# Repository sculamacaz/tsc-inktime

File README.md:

# InkTime

Author: Luca Mazilescu

## Block Diagram

## Hardware Functionality

### Microcontroller

The system is built around a Nordic **nRF52840** SoC (Arm Cortex-M4F @ 64 MHz, 1 MB flash, 256 kB RAM). It was chosen because it integrates a 2.4 GHz radio supporting Bluetooth Low Energy alongside a USB 2.0 full-speed controller, which covers both the wireless sync path and the USB-C data path without any external transceiver. The MCU runs from a 32 MHz high-frequency crystal (XC1/XC2) for the radio and CPU, and a 32.768 kHz low-frequency crystal (XL1/XL2) for the RTC and low-power sleep timing — accurate timekeeping is the whole point of a watch, so the LFXO is not optional.

An on-board 2.4 GHz chip antenna (2450AT18B100E) is placed at the edge of the PCB with a keep-out area underneath, fed from the `ANT` pin through a matching network.

### Display — E-Paper (SPI)

A reflective e-paper display is driven over **SPI** using SCK (P0.02), MOSI (P0.03) and a dedicated chip-select (P0.05). Three auxiliary GPIOs handle the panel-specific control lines: `EPD_DC` (P0.15) switches between command and data bytes, `EPD_RST` (P0.16) resets the display controller, and `EPD_BUSY` (P0.17) is an input the MCU polls while the panel completes a refresh. The display connects through a 24-pin FPC.

Because e-paper draws current only during a refresh (and essentially zero while displaying a static image), the entire display rail is gated by a PFET whose gate is driven from P1.01. Firmware can therefore cut power to the panel completely between updates, which is the dominant reason this watch can be expected to last days on a charge rather than hours.

### IMU — BMA421 (I²C)

A Bosch **BMA421** 3-axis accelerometer sits on the shared I²C bus. It provides raw acceleration data plus on-chip step counting functionality. Two interrupt lines, `IMU_INT1` (P0.08) and `IMU_INT2` (P1.08), let the sensor wake the MCU from deep sleep when a gesture or step event occurs, so the CPU does not have to poll the bus continuously.

### Haptics — DRV2605 (I²C)

A TI **DRV2605L** haptic driver actuates a coin LRA/ERM motor for notifications and UI feedback. It is configured over I²C and can play back effects from its internal ROM library, so the MCU only issues short "play effect N" commands rather than streaming waveforms. An enable line (`HAPTIC_EN`, P0.12) lets the MCU fully power the driver down when idle.

### Power management — BQ25180 + MAX17048 + RT6160

USB-C provides 5 V in through a USBLC6-2SC6Y ESD protector, with the two required 5.1 kΩ CC pull-downs advertising the device as a sink. A **BQ25180** single-cell Li-ion charger manages the LiPo battery: it handles CC/CV charging from USB, switches between USB and battery as the system source, and reports faults over I²C and on the `PMIC_INT` line (P0.11).

The system rail is generated by an **RT6160** buck-boost regulator producing a stable `3V3` across the full battery voltage range (~3.0–4.2 V), which is important because a plain buck would drop out near end-of-discharge and a plain boost would waste efficiency when the cell is full.

State-of-charge is tracked by a **MAX17048** fuel gauge directly on the battery node. It uses Maxim's ModelGauge algorithm, so no external current-sense resistor is needed — the MCU just reads the remaining percentage and cell voltage over I²C, and an `ALERT` line (P1.10) fires on programmable under/over-voltage thresholds.

### Inputs — Buttons

Three user buttons are connected to P0.13, P0.14 and P1.02 as active-low inputs with RC debounce. They use the MCU's internal pull-ups and can trigger GPIOTE interrupts to wake the device from System OFF.

### Shared I²C bus

All four I²C peripherals (BMA421, MAX17048, DRV2605L, BQ25180) share a single bus on SDA (P0.06) and SCL (P0.07), with 3.3 kΩ pull-ups to `3V3`. The devices have distinct 7-bit addresses, so one TWI instance on the nRF52840 is sufficient. Running I²C at 400 kHz (Fast-mode) is more than enough headroom for the low-bandwidth status reads these sensors require.

### Debug

An SWD interface (`SWDCLK`, `SWDIO`, optional `SWO` on P1.00) is exposed through a Tag-Connect TC2030 footprint, which avoids placing a bulky 2×5 header on a wearable-sized PCB.

### Expected capabilities

With the hardware described above, firmware would be able to: keep accurate time from the LFXO-backed RTC, render watch faces and menus on the e-paper display, detect steps and wrist-raise via the BMA421, deliver haptic notifications, communicate with a phone over BLE, enumerate as a USB device for charging and data, and report battery percentage and charger state in real time.

## Pinout Table

| Pin | Signal | Direction | Peripheral | Description |
|-----|--------|-----------|------------|-------------|
| P0.02 | SPI_SCK | Output | E-Paper Display | SPI clock |
| P0.03 | SPI_MOSI | Output | E-Paper Display | SPI data out |
| P0.05 | EPD_CS | Output | E-Paper Display | Chip select |
| P0.06 | SDA | Bidir | Fuel Gauge, Charger, IMU, Haptics | Shared I2C data |
| P0.07 | SCL | Output | Fuel Gauge, Charger, IMU, Haptics | Shared I2C clock |
| P0.08 | IMU_INT1 | Input | IMU (BMA421) | Interrupt line 1 |
| P0.11 | PMIC_INT | Input | Charger (BQ25180) | Fault/status interrupt |
| P0.12 | HAPTIC_EN | Output | Haptics (DRV2605) | Driver enable |
| P0.13 | — | Input | Button 1 | User button |
| P0.14 | — | Input | Button 2 | User button |
| P0.15 | EPD_DC | Output | E-Paper Display | Data/command select |
| P0.16 | EPD_RST | Output | E-Paper Display | Display reset |
| P0.17 | EPD_BUSY | Input | E-Paper Display | Busy status |
| P0.18 | RESET | Input | — | System reset |
| P1.00 | SWO | Output | Debug (pad) | SWD trace output |
| P1.01 | — | Output | EPD power gate | EPD power control |
| P1.02 | — | Input | Button 3 | User button |
| P1.08 | IMU_INT2 | Input | IMU (BMA421) | Interrupt line 2 |
| P1.10 | ALERT | Input | Fuel Gauge (MAX17048) | UV/OV alert |
| D+ | D+ | Bidir | USB-C connector | USB data+ |
| D− | D- | Bidir | USB-C connector | USB data− |
| XL1/XL2 | — | — | 32.768 kHz crystal | Low-frequency clock |
| XC1/XC2 | — | — | 32 MHz crystal | High-frequency clock |
| SWDCLK | SWDCLK | Input | Debug (pad) | SWD clock |
| SWDIO | SWDIO | Bidir | Debug (pad) | SWD data |
| ANT | RF | Output | 2.4 GHz antenna | Wireless antenna feed |

## Bill of Materials

The full, JLCPCB validated table can be found in `Assets/JLCPCB_BOM.xlsx`. That version contains detailed information about each part, such as the associated schematic designators, descriptions, and more.

| Part Name |Qty|Link (Order + Datasheet)|
| :-- | :--: | :--: |
|BMA421|1|[Link](https://jlcpcb.com/partdetail/BoschSensortec-BMA421/C5242966)|
|0201X104K100NT|5|[Link](https://jlcpcb.com/partdetail/270391-0201X104K100NT/C284966)|
|CGA0402X5R475M250GT|1|[Link](https://jlcpcb.com/partdetail/HRE-CGA0402X5R475M250GT/C6119795)|
|KH-TYPE-C-16P|1|[Link](https://jlcpcb.com/partdetail/Shenzhen_KinghelmElec-KH_TYPE_C16P/C709357)|
|RT6160AWSC|1|[Link](https://jlcpcb.com/partdetail/RichtekTech-RT6160AWSC/C7065276)|
|SDFL1608S100KTF|1|[Link](https://jlcpcb.com/partdetail/Sunlord-SDFL1608S100KTF/C1035)|
|0201WMF220KTEE|1|[Link](https://jlcpcb.com/partdetail/479910-0201WMF220KTEE/C473517)|
|EVPAKE31A|3|[Link](https://jlcpcb.com/partdetail/PANASONIC-EVPAKE31A/C569760)|
|GRM033R61A104KE15D|5|[Link](https://jlcpcb.com/partdetail/MurataElectronics-GRM033R61A104KE15D/C76934)|
|5034802400|1|[Link](https://jlcpcb.com/partdetail/MOLEX-5034802400/C122434)|
|CM8V-T1A-32.768KHZ-9PF-20PPM-TB-QA|1|[Link](https://jlcpcb.com/partdetail/C5366546)|
|BQ25180YBGR|1|[Link](https://jlcpcb.com/partdetail/TexasInstruments-BQ25180YBGR/C3682423)|
|DRV2605YZFR|1|[Link](https://jlcpcb.com/partdetail/TexasInstruments-DRV2605YZFR/C81079)|
|2450AT18B100E|1|[Link](https://jlcpcb.com/partdetail/JohansonDielectrics-2450AT18B100E/C2917717)|
|SI1308EDL-T1-GE3|1|[Link](https://jlcpcb.com/partdetail/VishayIntertech-SI1308EDL_T1GE3/C469327)|
|GRM155R60J226ME11D|2|[Link](https://jlcpcb.com/partdetail/408393-GRM155R60J226ME11D/C415703)|
|GRM155R61H105KE05D|9|[Link](https://jlcpcb.com/partdetail/1609005-GRM155R61H105KE05D/C1518208)|
|SDCL1005C15NJTDF|1|[Link](https://jlcpcb.com/partdetail/Sunlord-SDCL1005C15NJTDF/C27143)|
|0201WMJ0000TEE|3|[Link](https://jlcpcb.com/partdetail/259867-0201WMJ0000TEE/C270337)|
|CC0201KRX5R7BB473|1|[Link](https://jlcpcb.com/partdetail/YAGEO-CC0201KRX5R7BB473/C505465)|
|CL05A475MP5NRNC|5|[Link](https://jlcpcb.com/partdetail/24469-CL05A475MP5NRNC/C23733)|
|CL05A105KA5NQNC|6|[Link](https://jlcpcb.com/partdetail/53938-CL05A105KA5NQNC/C52923)|
|SDCL1005C3N9STDF|1|[Link](https://jlcpcb.com/partdetail/Sunlord-SDCL1005C3N9STDF/C14033)|
|CR0201FH5101G|2|[Link](https://jlcpcb.com/partdetail/LIZElec-CR0201FH5101G/C100142)|
|GRM0335C1H1R0BA01D|2|[Link](https://jlcpcb.com/partdetail/MurataElectronics-GRM0335C1H1R0BA01D/C85893)|
|CL05A106MQ5NUNC|3|[Link](https://jlcpcb.com/partdetail/16204-CL05A106MQ5NUNC/C15525)|
|0201CG120J500NT|4|[Link](https://jlcpcb.com/partdetail/51400-0201CG120J500NT/C50391)|
|BQ25180YBGR|1|[Link](https://jlcpcb.com/partdetail/TexasInstruments-BQ25180YBGR/C3682423)|
|MAX17048G+T10|1|[Link](https://jlcpcb.com/partdetail/2777647-MAX17048GT10/C2682616)|
|NX2016SA-32MHZ-STD-CZS-5|1|[Link](https://jlcpcb.com/partdetail/NDK-NX2016SA_32MHZ_STD_CZS5/C843260)|
|0201WMJ0332TEE|2|[Link](https://jlcpcb.com/partdetail/259848-0201WMJ0332TEE/C270318)|
|MBR0530|3|[Link](https://jlcpcb.com/partdetail/78464-MBR0530/C77336)|
|FTC252012SR47MBCA|1|[Link](https://jlcpcb.com/partdetail/6763488-FTC252012SR47MBCA/C5832368)|
|DMG2305UX-7|1|[Link](https://jlcpcb.com/partdetail/DiodesIncorporated-DMG2305UX7/C150470)|
|USBLC6-2SC6Y|1|[Link](https://jlcpcb.com/partdetail/TECHPUBLIC-USBLC62SC6Y/C5310974)|
|UCR006YVPFLR470|1|[Link](https://jlcpcb.com/partdetail/ROHMSemicon-UCR006YVPFLR470/C2089071)|
|CPF0201D10KC1|6|[Link](https://jlcpcb.com/partdetail/TEConnectivity-CPF0201D10KC1/C4187156)|
|744043680|1|[Link](https://jlcpcb.com/partdetail/WurthElektronik-744043680/C2045671)|
|GRM0335C1H101JA01D|1|[Link](https://jlcpcb.com/partdetail/MurataElectronics-GRM0335C1H101JA01D/C76922)|
|NRF52840-QIAA-R7|1|[Link](https://jlcpcb.com/partdetail/NordicSemicon-NRF52840_QIAAR7/C1851953)|

## Renders

## Design Details

### Schematic and Components

The reference schematic was double-checked with information from each component's datasheet.
Mismatches were flagged and investigated, usually stemming from older versions of the reference circuits being used by the reference schematic.

### PCB Layout and Routing

Manufacturing parameters were kept within the ranges recommended by JLCPCB's standard rigid PCB assembly service.

A top ground pour was stitched to the ground plane, and more granular manual stitching was performed around the antenna feed line.

Teardrops were generated at most trace joints, and angles were carefully considered during routing.
Since Fusion exhibits buggy behavior when generating teardrops for off-grid rotations,
the shapes were manually smoothed for traces in close proximity to the MCU,
since it's placed at 45 degrees.

Due to space constraints and the minimum recommended text height being 1mm,
the silkscreen uses an indexed legend to allow labeling in narrow areas.
ICs, pads, and any larger components have labels on the silkscreen.

In order to achieve mechanical robustness, internal annular rings were kept large.
To accomodate, some unused pins of the MCU's package were masked, thus electrically isolating them from any traces running below.

VIA-in-pad (ViP) was liberally used for the smaller SMD multi-pin components.
DRC errors stemming from ViP-related clearance were manually approved.

Spatial constraints like the antenna's keep out zone, crystal oscillator trace length,
and IMU-shaker distance maximization were carefully considered. Decoupling capacitors were also placed in close proximity to the relevant pins.

USB (D+, D-) lines were differentially routed, keeping lengths approximately equal, and the lines close together.

### 3D Design

Detailed models of every component were retreived and integrated into the 3D PCB model.

The full closed-case assembly was checked for mechanical interference.
A potential problem was found regarding the maximum height of the battery listed in its datasheet,
as the case's bottom cavity doesn't provide enough clearance below the PCB.
This may or may not be a problem in practice, the case was left as-is to be tested in a prototype.

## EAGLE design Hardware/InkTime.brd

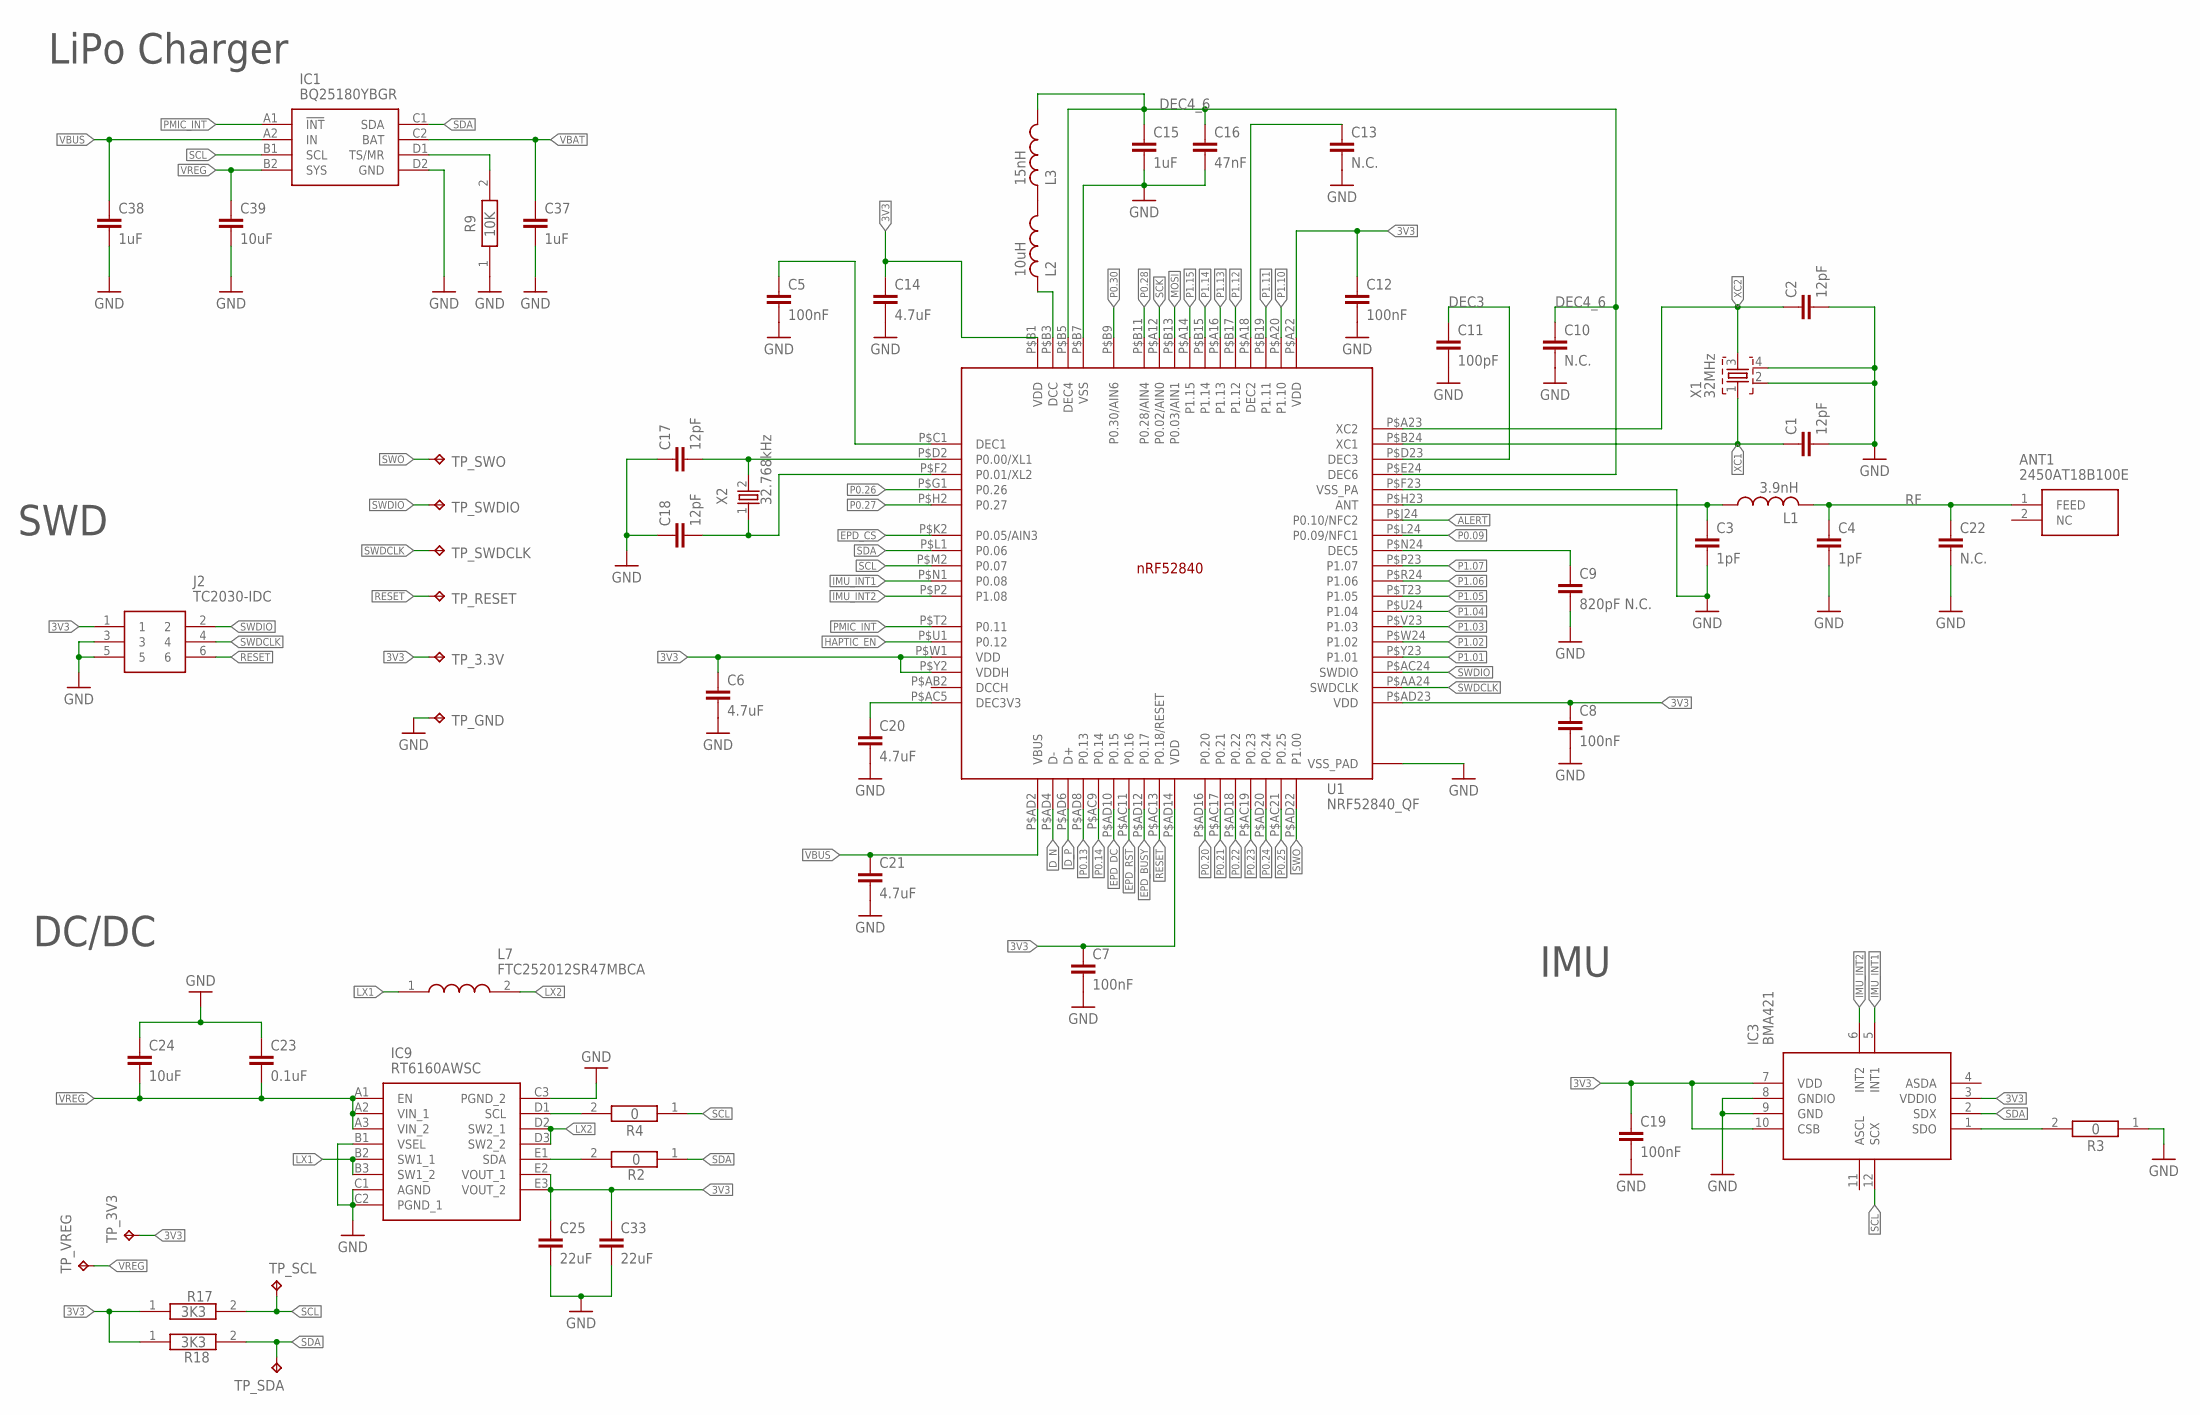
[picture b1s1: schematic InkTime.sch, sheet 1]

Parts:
ANT1: 2450AT18B100E; 2450AT18B100E_ANTC3216X140N
C1, C2, C17, C18: 12pF; NORDIC_NRF_3_RESC0201_N
C3, C4: 1pF; NORDIC_NRF_3_RESC0201_N
C5, C7, C8, C12, C19: 100nF; NORDIC_NRF_3_RESC0201_N
C6, C14, C20, C21: 4.7uF; NORDIC_NRF_3_RESC0402_N
C9: 820pF N.C.; NORDIC_NRF_3_RESC0201_N
C10, C13, C22: N.C.; NORDIC_NRF_3_RESC0201_N
C11: 100pF; NORDIC_NRF_3_RESC0201_N
C15, C37, C38: 1uF; NORDIC_NRF_3_RESC0402_N
C16: 47nF; NORDIC_NRF_3_RESC0201_N
C23: 0.1uF; NORDIC_NRF_3_RESC0201_N
C24, C39: 10uF; NORDIC_NRF_3_RESC0402_N
C25, C33: 22uF; NORDIC_NRF_3_RESC0402_N
IC1: BQ25180YBGR; BQ25180YBGR_BGA8C40P2X4_100X155X50
IC3: BMA421; BMA423_BMA423
IC9: RT6160AWSC; RT6160AWSC_BGA15C40P3X5_140X230X60
J2: TC2030-IDC; TC2030-IDC_TC2030IDC
L1: 3.9nH; NORDIC_NRF_2_RESC0402_N
L2: 10uH; NORDIC_NRF_2_RESC0603_N
L3: 15nH; NORDIC_NRF_2_RESC0402_N
L7: FTC252012SR47MBCA; MLP2016SR47MT0S1_INDC2016X100N
R2, R3, R4: 0; CPF0201D7K68C1_0201
R9: 10K; CPF0201D7K68C1_0201
R17, R18: 3K3; CPF0201D7K68C1_0201
TP_3.3V, TP_3V3: HECTOR_WATCH_1_TPTP20R; HECTOR_WATCH_1_TP20R
TP_GND: HECTOR_WATCH_1_TPTP20R; HECTOR_WATCH_1_TP20R
TP_RESET: HECTOR_WATCH_1_TPTP20R; HECTOR_WATCH_1_TP20R
TP_SCL: HECTOR_WATCH_1_TPTP20R; HECTOR_WATCH_1_TP20R
TP_SDA: HECTOR_WATCH_1_TPTP20R; HECTOR_WATCH_1_TP20R
TP_SWDCLK: HECTOR_WATCH_1_TPTP20R; HECTOR_WATCH_1_TP20R
TP_SWDIO: HECTOR_WATCH_1_TPTP20R; HECTOR_WATCH_1_TP20R
TP_SWO: HECTOR_WATCH_1_TPTP20R; HECTOR_WATCH_1_TP20R
TP_VREG: HECTOR_WATCH_1_TPTP20R; HECTOR_WATCH_1_TP20R
U1: NRF52840_QF; NORDIC_NRF_4_AQFN50P700X700X85_HS-74N_PINCLEAN2
X1: 32MHz; NORDIC_NRF_BT-XTAL_2016_N
X2: 32.768kHz; NORDIC_NRF_1_XTAL_3215_N

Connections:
3V3: C6.1, C7.1, C8.1, C12.1, C14.1, C19.1, C25.1, C33.1, IC3.3 (VDDIO), IC3.7 (VDD), IC3.10 (CSB), IC9.E2 (VOUT_1), IC9.E3 (VOUT_2), J2.1, R17.1, R18.1, TP_3.3V.TP, TP_3V3.TP, U1.P$A22 (VDD), U1.P$AD14 (VDD), U1.P$AD23 (VDD), U1.P$B1 (VDD), U1.P$W1 (VDD), U1.P$Y2 (VDDH); also elsewhere on the board
ALERT: U1.P$J24 (P0.10/NFC2); also elsewhere on the board
DEC3: C11.1, U1.P$D23 (DEC3)
DEC4_6: C10.1, C15.1, C16.1, L3.1, U1.P$B5 (DEC4), U1.P$E24 (DEC6)
D_N: U1.P$AD4 (D-); also elsewhere on the board
D_P: U1.P$AD6 (D+); also elsewhere on the board
EPD_BUSY: U1.P$AD12 (P0.17); also elsewhere on the board
EPD_CS: U1.P$K2 (P0.05/AIN3); also elsewhere on the board
EPD_DC: U1.P$AD10 (P0.15); also elsewhere on the board
EPD_RST: U1.P$AC11 (P0.16); also elsewhere on the board
GND: C1.2, C2.2, C3.2, C4.2, C5.2, C6.2, C7.2, C8.2, C9.2, C10.2, C11.2, C12.2, C13.2, C14.2, C15.2, C16.2, C17.1, C18.1, C19.2, C20.2, C21.2, C22.2, C23.1, C24.1, C25.2, C33.2, C37.2, C38.2, C39.2, IC1.D2 (GND), IC3.8 (GNDIO), IC3.9 (GND), IC9.B1 (VSEL), IC9.C1 (AGND), IC9.C2 (PGND_1), IC9.C3 (PGND_2), J2.3, J2.5, R3.1, R9.1, TP_GND.TP, U1.P$74 (VSS_PAD), U1.P$75 (VSS_PAD), U1.P$76 (VSS_PAD), U1.P$77 (VSS_PAD), U1.P$78 (VSS_PAD), U1.P$79 (VSS_PAD), U1.P$80 (VSS_PAD), U1.P$81 (VSS_PAD), U1.P$82 (VSS_PAD), U1.P$83 (VSS_PAD), U1.P$84 (VSS_PAD), U1.P$85 (VSS_PAD), U1.P$86 (VSS_PAD), U1.P$87 (VSS_PAD), U1.P$88 (VSS_PAD), U1.P$89 (VSS_PAD), U1.P$90 (VSS_PAD), U1.P$B7 (VSS), U1.P$F23 (VSS_PA), X1.2, X1.4; also elsewhere on the board
HAPTIC_EN: U1.P$U1 (P0.12); also elsewhere on the board
IMU_INT1: IC3.5 (INT1), U1.P$N1 (P0.08)
IMU_INT2: IC3.6 (INT2), U1.P$P2 (P1.08)
LX1: IC9.B2 (SW1_1), IC9.B3 (SW1_2), L7.1
LX2: IC9.D2 (SW2_1), IC9.D3 (SW2_2), L7.2
MOSI: U1.P$B13 (P0.03/AIN1); also elsewhere on the board
unnamed: L2.1, L3.2
unnamed: L2.2, U1.P$B3 (DCC)
unnamed: IC1.D1 (TS/MR), R9.2
unnamed: C3.1, L1.1, U1.P$H23 (ANT)
unnamed: C9.1, U1.P$N24 (DEC5)
unnamed: C17.2, U1.P$D2 (P0.00/XL1), X2.2
unnamed: C5.1, U1.P$C1 (DEC1)
unnamed: IC9.E1 (SDA), R2.2
unnamed: C20.1, U1.P$AC5 (DEC3V3)
unnamed: IC9.D1 (SCL), R4.2
unnamed: IC3.1 (SDO), R3.2
unnamed: C18.2, U1.P$F2 (P0.01/XL2), X2.1
unnamed: C13.1, U1.P$A18 (DEC2)
P0.09: U1.P$L24 (P0.09/NFC1)
P0.13: U1.P$AD8 (P0.13); also elsewhere on the board
P0.14: U1.P$AC9 (P0.14); also elsewhere on the board
P0.20: U1.P$AD16 (P0.20)
P0.21: U1.P$AC17 (P0.21)
P0.22: U1.P$AD18 (P0.22)
P0.23: U1.P$AC19 (P0.23)
P0.24: U1.P$AD20 (P0.24)
P0.25: U1.P$AC21 (P0.25)
P0.26: U1.P$G1 (P0.26)
P0.27: U1.P$H2 (P0.27)
P0.28: U1.P$B11 (P0.28/AIN4)
P0.30: U1.P$B9 (P0.30/AIN6)
P1.01: U1.P$Y23 (P1.01); also elsewhere on the board
P1.02: U1.P$W24 (P1.02); also elsewhere on the board
P1.03: U1.P$V23 (P1.03)
P1.04: U1.P$U24 (P1.04)
P1.05: U1.P$T23 (P1.05)
P1.06: U1.P$R24 (P1.06)
P1.07: U1.P$P23 (P1.07)
P1.10: U1.P$A20 (P1.10)
P1.11: U1.P$B19 (P1.11)
P1.12: U1.P$B17 (P1.12)
P1.13: U1.P$A16 (P1.13)
P1.14: U1.P$B15 (P1.14)
P1.15: U1.P$A14 (P1.15)
PMIC_INT: IC1.A1 (!INT), U1.P$T2 (P0.11)
RESET: J2.6, TP_RESET.TP, U1.P$AC13 (P0.18/RESET)
RF: ANT1.1 (FEED), C4.1, C22.1, L1.2
SCK: U1.P$A12 (P0.02/AIN0); also elsewhere on the board
SCL: IC1.B1 (SCL), IC3.12 (SCX), R4.1, R17.2, TP_SCL.TP, U1.P$M2 (P0.07); also elsewhere on the board
SDA: IC1.C1 (SDA), IC3.2 (SDX), R2.1, R18.2, TP_SDA.TP, U1.P$L1 (P0.06); also elsewhere on the board
SWDCLK: J2.4, TP_SWDCLK.TP, U1.P$AA24 (SWDCLK)
SWDIO: J2.2, TP_SWDIO.TP, U1.P$AC24 (SWDIO)
SWO: TP_SWO.TP, U1.P$AD22 (P1.00)
VBAT: C37.1, IC1.C2 (BAT); also elsewhere on the board
VBUS: C21.1, C38.1, IC1.A2 (IN), U1.P$AD2 (VBUS); also elsewhere on the board
VREG: C23.2, C24.2, C39.1, IC1.B2 (SYS), IC9.A1 (EN), IC9.A2 (VIN_1), IC9.A3 (VIN_2), TP_VREG.TP
XC1: C1.1, U1.P$B24 (XC1), X1.1
XC2: C2.1, U1.P$A23 (XC2), X1.3

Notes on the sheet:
LiPo Charger
DC/DC
IMU
SWD

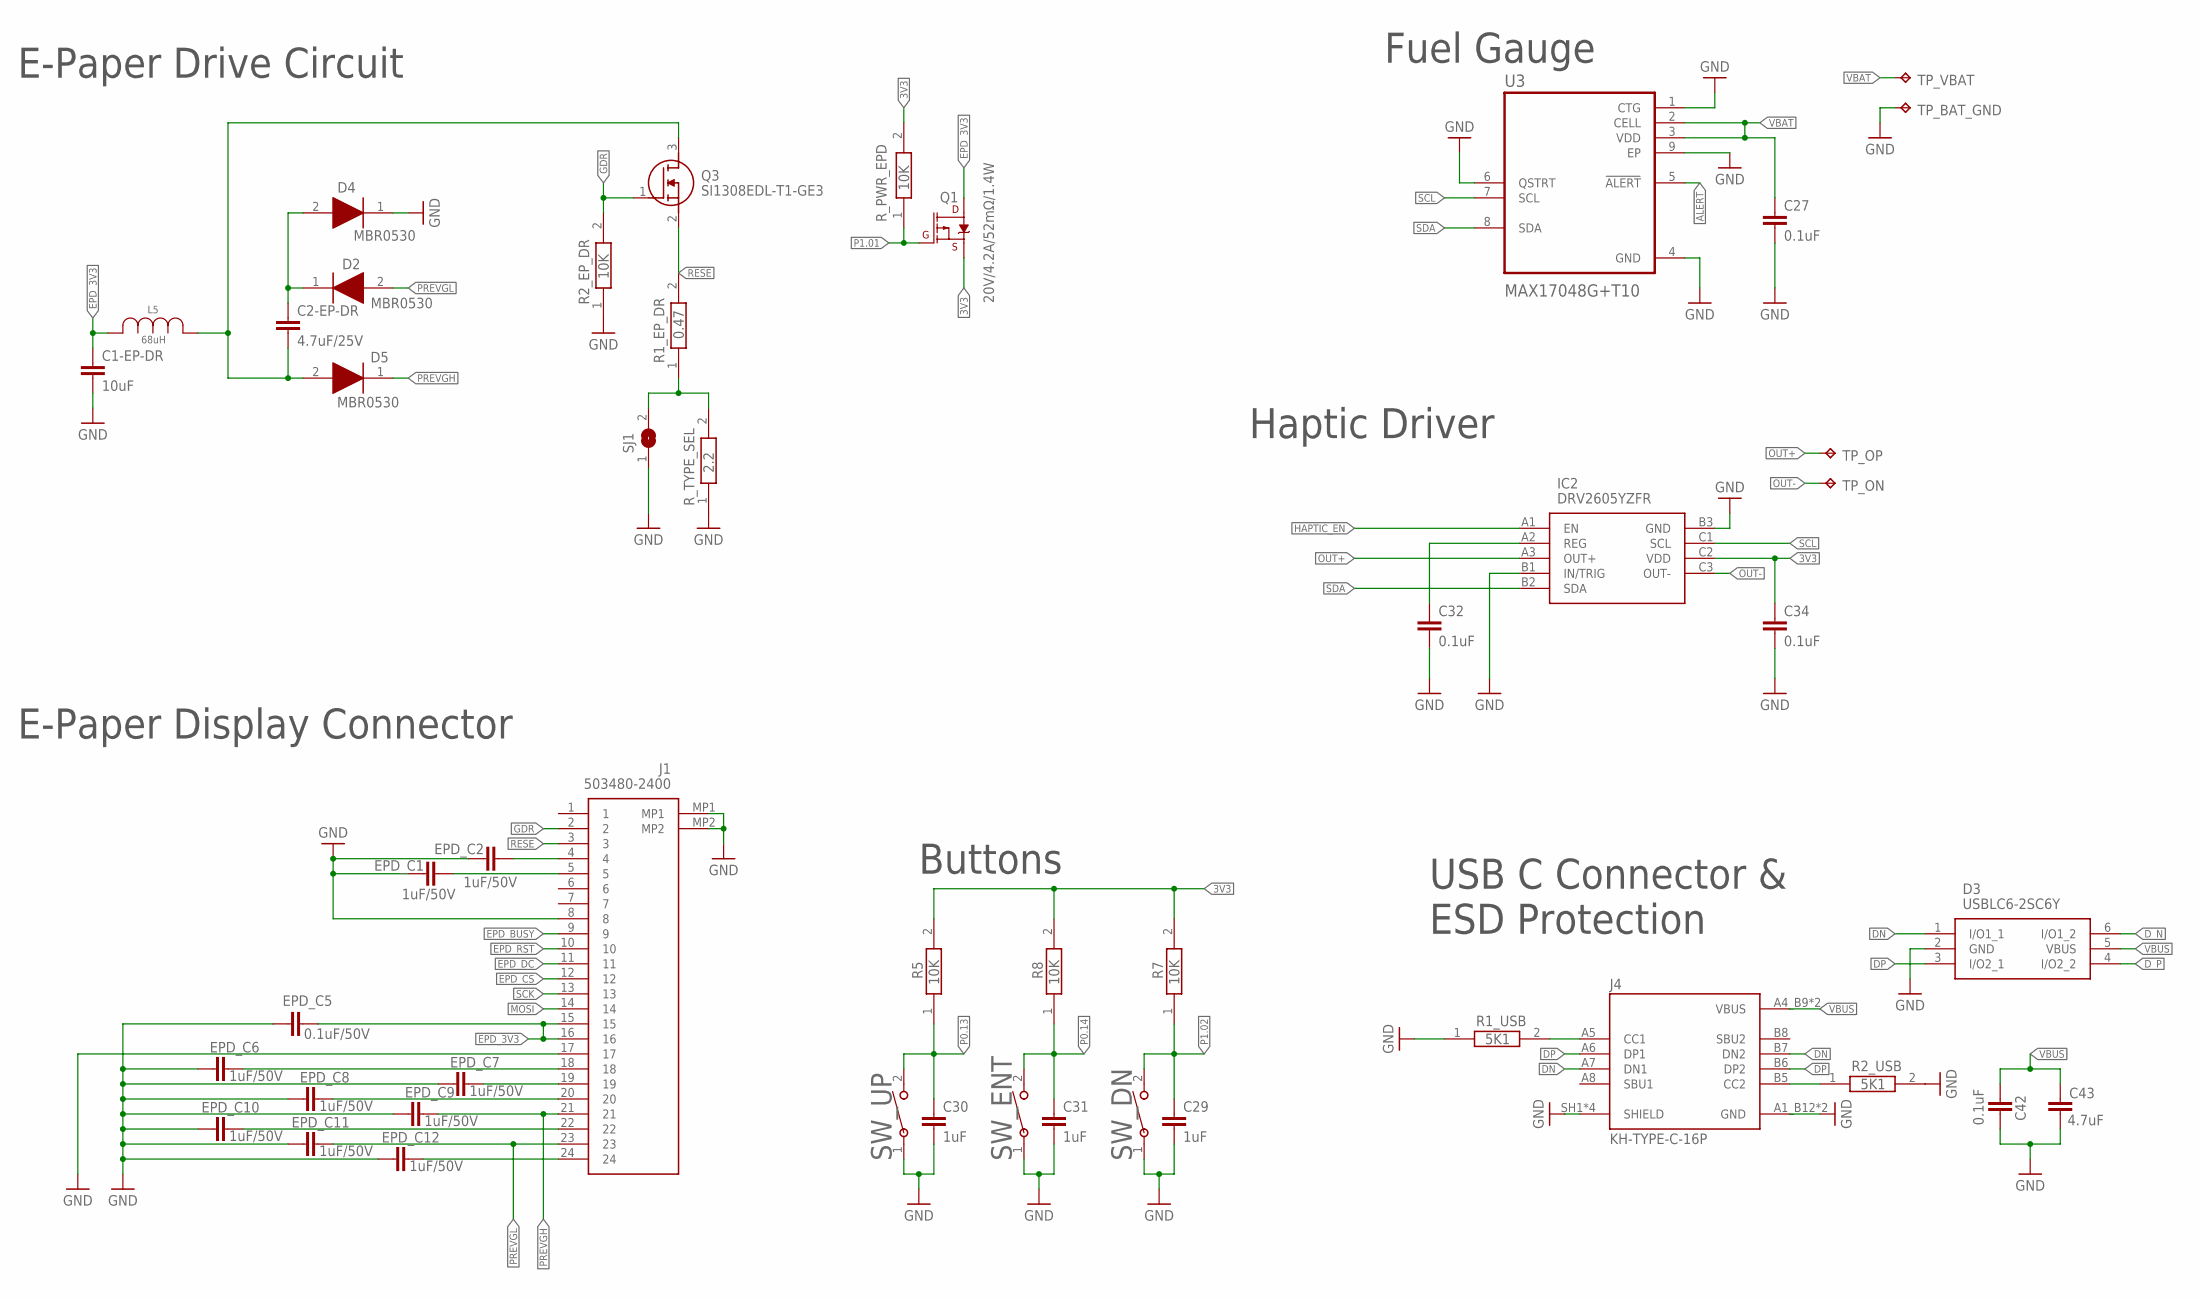
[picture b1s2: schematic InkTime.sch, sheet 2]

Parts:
C1-EP-DR: 10uF; NORDIC_NRF_3_RESC0402_N
C2-EP-DR: 4.7uF/25V; NORDIC_NRF_3_RESC0402_N
C27, C32, C34, C42: 0.1uF; NORDIC_NRF_3_RESC0201_N
C29, C30, C31: 1uF; NORDIC_NRF_3_RESC0402_N
C43: 4.7uF; NORDIC_NRF_3_RESC0402_N
D2, D4, D5: MBR0530; ESP32_C6_LIBRARY_5_SOD3716X135N
D3: USBLC6-2SC6Y; ESP32_C6_LIBRARY_3_SOT95P280X145-6N
EPD_C1, EPD_C2, EPD_C6, EPD_C7, EPD_C8, EPD_C9, EPD_C10, EPD_C11, EPD_C12: 1uF/50V; NORDIC_NRF_3_RESC0402_N
EPD_C5: 0.1uF/50V; NORDIC_NRF_3_RESC0402_N
IC2: DRV2605YZFR; DRV2605YZFR_BGA9C50P3X3_144X144X62
J1: 503480-2400; 503480-2400_5034802400
J4: KH-TYPE-C-16P; KH-TYPE-C-16P_KINGHELM_KH-TYPE-C-16P
L5: 68uH; ESP32_C6_LIBRARY_2_IND_4828-WE-TPC_WRE
Q1: 20V/4.2A/52mΩ/1.4W; ESP32_C6_LIBRARY_4_ESP32_C6_LIBRARY_4_ESP32_C6_LIBRARY_4_ES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
Q3: SI1308EDL-T1-GE3; ESP32_C6_LIBRARY_6_SOT65P210X110-3N
R1_EP_DR: 0.47; CPF0201D7K68C1_0201
R1_USB, R2_USB: 5K1; CPF0201D7K68C1_0201
R2_EP_DR, R5, R7, R8: 10K; CPF0201D7K68C1_0201
R_PWR_EPD: 10K; CPF0201D7K68C1_0201
R_TYPE_SEL: 2.2; CPF0201D7K68C1_0201
SJ1: ESP32_C6_LIBRARY_7_JUMPER_SJ
SW_DN: 2025-10-22_07-23-44_LIBRARY_EVP-AKE31ASW_EVP-AKE3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; 2025-10-22_07-23-44_LIBRARY_SW_EVP-AKE31A_PAN
SW_ENT: 2025-10-22_07-23-44_LIBRARY_EVP-AKE31ASW_EVP-AKE3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; 2025-10-22_07-23-44_LIBRARY_SW_EVP-AKE31A_PAN
SW_UP: 2025-10-22_07-23-44_LIBRARY_EVP-AKE31ASW_EVP-AKE3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; 2025-10-22_07-23-44_LIBRARY_SW_EVP-AKE31A_PAN
TP_BAT_GND: HECTOR_WATCH_1_TPTP20R; HECTOR_WATCH_1_TP20R
TP_ON: HECTOR_WATCH_1_TPTP20R; HECTOR_WATCH_1_TP20R
TP_OP: HECTOR_WATCH_1_TPTP20R; HECTOR_WATCH_1_TP20R
TP_VBAT: HECTOR_WATCH_1_TPTP20R; HECTOR_WATCH_1_TP20R
U3: MAX17048G+T10; ESP32_C6_LIBRARY_SON50P200X200X80-9N

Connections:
3V3: C34.1, IC2.C2 (VDD), Q1.2 (S), R5.2, R7.2, R8.2, R_PWR_EPD.2; also elsewhere on the board
ALERT: U3.5 (!ALERT); also elsewhere on the board
DN: D3.1 (I/O1_1), J4.A7 (DN1), J4.B7 (DN2)
DP: D3.3 (I/O2_1), J4.A6 (DP1), J4.B6 (DP2)
D_N: D3.6 (I/O1_2); also elsewhere on the board
D_P: D3.4 (I/O2_2); also elsewhere on the board
EPD_3V3: C1-EP-DR.1, EPD_C5.2, J1.15, J1.16, L5.2, Q1.3 (D)
EPD_BUSY: J1.9; also elsewhere on the board
EPD_CS: J1.12; also elsewhere on the board
EPD_DC: J1.11; also elsewhere on the board
EPD_RST: J1.10; also elsewhere on the board
GDR: J1.2, Q3.1 (G), R2_EP_DR.2
GND: C1-EP-DR.2, C27.2, C29.2, C30.2, C31.2, C32.2, C34.2, C42.2, C43.2, D3.2 (GND), D4.1 (K), EPD_C1.1, EPD_C2.1, EPD_C5.1, EPD_C6.1, EPD_C7.1, EPD_C8.1, EPD_C9.1, EPD_C10.1, EPD_C11.1, EPD_C12.1, IC2.B1 (IN/TRIG), IC2.B3 (GND), J1.8, J1.17, J1.MP1, J1.MP2, J4.A1_B12 (GND), J4.A12_B1 (GND), J4.SH1 (SHIELD), J4.SH2 (SHIELD), J4.SH3 (SHIELD), J4.SH4 (SHIELD), R1_USB.1, R2_EP_DR.1, R2_USB.2, R_TYPE_SEL.1, SJ1.1, SW_DN.1, SW_ENT.1, SW_UP.1, TP_BAT_GND.TP, U3.1 (CTG), U3.4 (GND), U3.6 (QSTRT), U3.9 (EP); also elsewhere on the board
HAPTIC_EN: IC2.A1 (EN); also elsewhere on the board
MOSI: J1.14; also elsewhere on the board
unnamed: J4.A5 (CC1), R1_USB.2
unnamed: EPD_C2.2, J1.4
unnamed: R1_EP_DR.1, R_TYPE_SEL.2, SJ1.2
unnamed: EPD_C1.2, J1.5
unnamed: C2-EP-DR.2, D5.2 (A), L5.1, Q3.3 (D)
unnamed: C32.1, IC2.A2 (REG)
unnamed: C2-EP-DR.1, D2.1 (K), D4.2 (A)
unnamed: J4.B5 (CC2), R2_USB.1
unnamed: EPD_C6.2, J1.18
unnamed: EPD_C7.2, J1.19
unnamed: EPD_C8.2, J1.20
unnamed: EPD_C10.2, J1.22
unnamed: EPD_C12.2, J1.24
OUT+: IC2.A3 (OUT+), TP_OP.TP
OUT-: IC2.C3 (OUT-), TP_ON.TP
P0.13: C30.1, R5.1, SW_UP.2; also elsewhere on the board
P0.14: C31.1, R8.1, SW_ENT.2; also elsewhere on the board
P1.01: Q1.1 (G), R_PWR_EPD.1; also elsewhere on the board
P1.02: C29.1, R7.1, SW_DN.2; also elsewhere on the board
PREVGH: D5.1 (K), EPD_C9.2, J1.21
PREVGL: D2.2 (A), EPD_C11.2, J1.23
RESE: J1.3, Q3.2 (S), R1_EP_DR.2
SCK: J1.13; also elsewhere on the board
SCL: IC2.C1 (SCL), U3.7 (SCL); also elsewhere on the board
SDA: IC2.B2 (SDA), U3.8 (SDA); also elsewhere on the board
VBAT: C27.1, TP_VBAT.TP, U3.2 (CELL), U3.3 (VDD); also elsewhere on the board
VBUS: C42.1, C43.1, D3.5 (VBUS), J4.A4_B9 (VBUS), J4.A9_B4 (VBUS); also elsewhere on the board

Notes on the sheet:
E-Paper Drive Circuit
E-Paper Display Connector
Fuel Gauge
Haptic Driver
Buttons
USB C Connector & ESD Protection

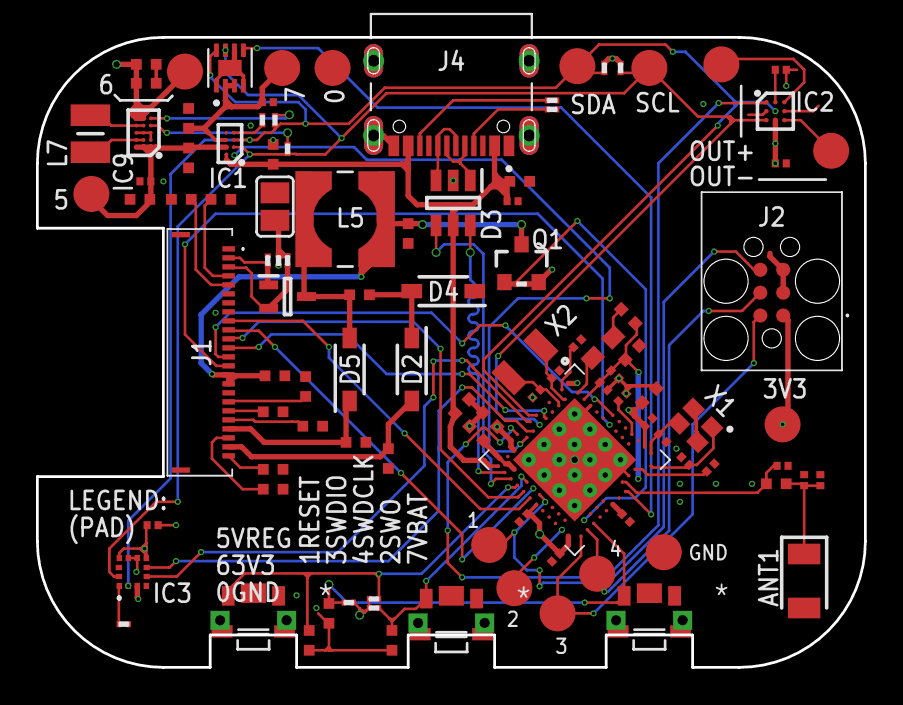
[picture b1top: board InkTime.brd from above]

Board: 4 copper layers, 46.0 x 35.0 mm, 105 parts (0 on the bottom side), 70 nets.

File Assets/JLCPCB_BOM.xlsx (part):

JLCPCB BOM Tool - BOM Matching
BOM name：bom-JLCPCB Assembly Order.xlsx |  |  |  | Download Time：2026-04-15 00:02:17 |  |  |  | * Our matching results are updated in real-time, but stock and prices may chang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
PCB Assembled Qty：5 |  |  |  | Est. Total Price：143.8173 (Pre-order parts require a quotation for final pricin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
Your BOM |  |  |  | Matched Parts |  |  |  |  |  |  | Order Information
Designator | Comment | Footprint | JLCPCB Part # | Matches | Part # | Manufacturer | Footprint | Description | Category | Warning | JLCPCB Part # | Product link | Source | Lib Type | MOQ | Availability | My Parts(JLCPCB Parts) | My Parts(Global sourcing & consigned parts) | Rec. Order Qty | Unit Price ($) | Total Price ($)
IC3 | BMA423 | LGA12 |  | Unconfirmed | BMA421 | Bosch Sensortec | LGA12 | LGA-12(2x2) Accelerometers ROHS | Accelerometers |  | C5242966 | https://jlcpcb.com/partdetail/BoschSensortec-BMA421/C5242966 | In-stock | Extended | 1 | 2037 | 0 | 0 | 5 | 0.841 | 4.205
C23,C27,C32,C34,C42 | 0.1uF | 0201 |  | Unconfirmed | 0201X104K100NT | FH (Guangdong Fenghua Advanced Tech) | 0201 | 100nF 10V X5R ±10% 0201 Multilayer Ceramic Capacitors MLCC - SMD/SMT ROHS | Multilayer Ceramic Capacitors MLCC - SMD/SMT | 1.The comment (0201X104K100NT) of this part does not match the one (0.1uF) prov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 | C284966 | https://jlcpcb.com/partdetail/270391-0201X104K100NT/C284966 | In-stock | Extended | 1 | 1767408 | 0 | 0 | 37 | 0.0008 | 0.0296
C2-EP-DR | 4.7uF/25V | 0402 |  | Unconfirmed | CGA0402X5R475M250GT | HRE | 0402 | 25V 4.7uF X5R ±20% 0402 Multilayer Ceramic Capacitors MLCC - SMD/SMT ROHS | Multilayer Ceramic Capacitors MLCC - SMD/SMT | 1.The comment (CGA0402X5R475M250GT) of this part does not match the one (4.7uF/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 | C6119795 | https://jlcpcb.com/partdetail/HRE-CGA0402X5R475M250GT/C6119795 | In-stock | Extended | 1 | 515427 | 0 | 0 | 15 | 0.0132 | 0.198
J4 | KH-TYPE-C-16P | SMD |  | Select by System | KH-TYPE-C-16P | Shenzhen Kinghelm Elec | SMD | -40℃~+85℃ 1 10,000 cycles 16P 30V 3A 7.81mm Female Surface Mount, Right Angle T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 | USB Connectors |  | C709357 | https://jlcpcb.com/partdetail/Shenzhen_KinghelmElec-KH_TYPE_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 | In-stock | Extended | 1 | 250180 | 0 | 0 | 5 | 0.076 | 0.38
IC9 | RT6160AWSC | 15-UFBGA,WLCSP |  | Select by System | RT6160AWSC | Richtek Tech | 15-UFBGA,WLCSP | -40℃~+125℃ 1 1uA 2.025V~5.2V 2.2MHz 2.2V~5.5V 3A Adjustable Buck-Boost Buck-Boo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 | DC-DC Converters |  | C7065276 | https://jlcpcb.com/partdetail/RichtekTech-RT6160AWSC/C7065276 | In-stock | Extended | 1 | 5993 | 0 | 0 | 5 | 0.5868 | 2.934
L2 | 10uH | 0603 |  | Unconfirmed | SDFL1608S100KTF | Sunlord | 0603 | 1.85Ω 10uH 17MHz 30@2MHz 3mA ±10% 0603 Inductors (SMD) ROHS | Inductors (SMD) | 1.The comment (SDFL1608S100KTF) of this part does not match the one (10uH) prov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 | C1035 | https://jlcpcb.com/partdetail/Sunlord-SDFL1608S100KTF/C1035 | In-stock | Basic | 1 | 314612 | 0 | 0 | 20 | 0.0175 | 0.35
R_TYPE_SEL | 2.2Ω | 0201 |  | Select by System | 0201WMF220KTEE | UNI-ROYAL(Uniroyal Elec) | 0201 | -100ppm/℃~+350ppm/℃ -55℃~+155℃ 2.2Ω 25V 50mW Thick Film Resistor ±1% 0201 Chip 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 | Chip Resistor - Surface Mount |  | C473517 | https://jlcpcb.com/partdetail/479910-0201WMF220KTEE/C473517 | In-stock | Extended | 1 | 489132 | 0 | 0 | 20 | 0.0012 | 0.024
SW_DN,SW_ENT,SW_UP | EVPAKE31A | SMD,3.9x2.9mm |  | Unconfirmed | EVPAKE31A | PANASONIC | SMD,3.9x2.9mm | -40℃~+85℃ 1.6N 1.6mm 15V 2.9mm 20mA 3.9mm 500,000 Cycles IP67 J-Lead Rectangula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 | Tactile Switches | 1.There may be multiple types of parts, but one type of part has been matched. 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 | C569760 | https://jlcpcb.com/partdetail/PANASONIC-EVPAKE31A/C569760 | In-stock | Extended | 1 | 26113 | 0 | 0 | 17 | 0.1596 | 2.7132
C5,C7,C8,C12,C19 | 100nF | 0201 |  | Unconfirmed | GRM033R61A104KE15D | Murata Electronics | 0201 | 100nF 10V X5R ±10% 0201 Multilayer Ceramic Capacitors MLCC - SMD/SMT ROHS | Multilayer Ceramic Capacitors MLCC - SMD/SMT | 1.The comment (GRM033R61A104KE15D) of this part does not match the one (100nF) 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 | C76934 | https://jlcpcb.com/partdetail/MurataElectronics-GRM033R61A10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 | In-stock | Extended | 1 | 1241377 | 0 | 0 | 37 | 0.002 | 0.074
J1 | 5034802400 | SMD,P=0.5mm, right angle |  | Select by System | 5034802400 | MOLEX | SMD,P=0.5mm, right angle | -40℃~+105℃ 0.3mm 0.5mm 1mm 24P 500mA 50V Double-Sided Contacts, Top and Bottom 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 | FFC, FPC (Flat Flexible) Connector Assemblies |  | C122434 | https://jlcpcb.com/partdetail/MOLEX-5034802400/C122434 | In-stock | Extended | 1 | 21 | 0 | 0 | 5 | 0.849 | 4.245
X2 | 32.768kHz | SMD,3.2x1.5mm |  | Select by System | CM8V-T1A-32.768KHZ-9PF-20PPM-TB-QA | Micro Crystal | SMD,3.2x1.5mm | -40℃~+125℃ 32.768kHz 70kΩ 9pF ±20ppm SMD2012-2P Crystals ROHS | Crystals |  | C5366546 | https://jlcpcb.com/partdetail/C5366546 | In-stock | Extended | 1 | 2791 | 0 | 0 | 5 | 0.6203 | 3.1015
EPD_C5 | 0.1uF/50V | 0402 |  | Unconfirmed | BQ25180YBGR | Texas Instruments | 0402 | -40℃~+125℃ 1 1A 3.2uA 4.65V 5.5V Charging IC I2C Lithium Battery、LiFePO4 Batter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 | Battery Management | 1.The footprint (DSBGA-8(1.1x1.6)) of this part does not match the one (0402) p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 | C3682423 | https://jlcpcb.com/partdetail/TexasInstruments-BQ25180YBGR/C3682423 | In-stock | Extended | 1 | 969 | 0 | 0 | 10 | 1.7954 | 17.954
IC2 | DRV2605YZFR | BGA9 |  | Select by System | DRV2605YZFR | Texas Instruments | BGA9 | -40℃~+85℃ 2.5V~5.5V I2C DSBGA-9 Brushed DC Motor Drivers ROHS | Brushed DC Motor Drivers |  | C81079 | https://jlcpcb.com/partdetail/TexasInstruments-DRV2605YZFR/C81079 | In-stock | Extended | 1 | 334 | 0 | 0 | 5 | 1.3286 | 6.643
ANT1 | 2450AT18B100E | 1206 |  | Select by System | 2450AT18B100E | Johanson Dielectrics | 1206 | -45℃~+125℃ 0.5dBi 1.3mm 1.6mm 100MHz 2.45GHz 2W 3.2mm 50Ω Patch Antenna 1206 An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 | Antennas |  | C2917717 | https://jlcpcb.com/partdetail/JohansonDielectrics-2450AT18B1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 | In-stock | Extended | 1 | 317 | 0 | 0 | 5 | 1.0408 | 5.204
Q3 | SI1308EDL-T1-GE3 | SOT-323 |  | Select by System | SI1308EDL-T1-GE3 | Vishay Intertech | SOT-323 | -55℃~+150℃ 1 N-channel 1.4nC@10V 1.5A 1.5V 105pF 11pF 132mΩ@10V 23pF 30V 400mW 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 | MOSFETs |  | C469327 | https://jlcpcb.com/partdetail/VishayIntertech-SI1308EDL_T1GE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 | In-stock | Extended | 1 | 16217 | 0 | 0 | 7 | 0.1853 | 1.2971
C25,C33 | 22uF | 0402 |  | Unconfirmed | GRM155R60J226ME11D | Murata Electronics | 0402 | 22uF 6.3V X5R ±20% 0402 Multilayer Ceramic Capacitors MLCC - SMD/SMT ROHS | Multilayer Ceramic Capacitors MLCC - SMD/SMT | 1.The comment (GRM155R60J226ME11D) of this part does not match the one (22uF) p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 | C415703 | https://jlcpcb.com/partdetail/408393-GRM155R60J226ME11D/C415703 | In-stock | Extended | 1 | 282949 | 0 | 0 | 14 | 0.0435 | 0.609
EPD_C1,EPD_C2,EPD_C6,EPD_C7,EPD_C8,EPD_C9,EPD_C10,EPD_C11,EPD_C12 | 1uF/50V | 0402 |  | Select by System | GRM155R61H105KE05D | Murata Electronics | 0402 | 1uF 50V X5R ±10% 0402 Multilayer Ceramic Capacitors MLCC - SMD/SMT ROHS | Multilayer Ceramic Capacitors MLCC - SMD/SMT |  | C1518208 | https://jlcpcb.com/partdetail/1609005-GRM155R61H105KE05D/C1518208 | In-stock | Extended | 1 | 264318 | 0 | 0 | 49 | 0.0304 | 1.4896
L3 | 15nH | 0402 |  | Unconfirmed | SDCL1005C15NJTDF | Sunlord | 0402 | 15nH 2.3GHz 300mA 500mΩ 8@100MHz ±5% 0402 Inductors (SMD) ROHS | Inductors (SMD) | 1.The comment (SDCL1005C15NJTDF) of this part does not match the one (15nH) pro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 | C27143 | https://jlcpcb.com/partdetail/Sunlord-SDCL1005C15NJTDF/C27143 | In-stock | Extended | 1 | 481616 | 0 | 0 | 20 | 0.0053 | 0.106
R2,R3,R4 | 0Ω | 0201 |  | Select by System | 0201WMJ0000TEE | UNI-ROYAL(Uniroyal Elec) | 0201 | -55℃~+155℃ 0Ω 25V 50mW Thick Film Resistor ±5% 0201 Chip Resistor - Surface Mou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 | Chip Resistor - Surface Mount |  | C270337 | https://jlcpcb.com/partdetail/259867-0201WMJ0000TEE/C270337 | In-stock | Extended | 1 | 908769 | 0 | 0 | 25 | 0.0008 | 0.02
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
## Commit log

2026-04-10 feat: add renders
2026-04-10 feat: improve case render
2026-04-10 fix: .DS_Store
2026-04-13 fix: 0.47Ohm resistor identification
2026-04-13 feat: block diagram, pinout table
2026-04-14 feat: finish README sections
    - add hardware functionality description
    - add BOM table + external full BOM
    - add renders
    - add design details
2026-04-14 fix: BMA423 -> BMA421
2026-04-19 fix: mask P0.19 from nRF package
2026-04-19 feat: add printout

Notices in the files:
parts and their libraries:
COPYRIGHT: Copyright (C) 2024 Ultra Librarian. All rights reserved.
COPYRIGHT: Copyright (C) 2025 Ultra Librarian. All rights reserved.
